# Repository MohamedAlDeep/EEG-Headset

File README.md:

# ADS1299 EEG Headset 🧠
This is a DIY / custom *electroencephalogram* reading device which is connected eeg electrodes that can connect to brain at designated areas.

It reads brain wave signals and digitizes them into the computer which is called brain-computer interface.

### Why am i doing this
I have a larger project and i want to join the competition with my pcb.

### The schematic 
This is the board schematic.

### PCB

### Mounting Part

### BOM 

| Item                  | Recommended_LCSC_PN   | Package        | JLCPCB_Type           | URL                                                                                                                                                                                                                                                                                                                                                                                                                                                                                                                                                                                                                                      | Unit Price   | Amount   | Total   |
|:----------------------|:----------------------|:---------------|:----------------------|:-----------------------------------------------------------------------------------------------------------------------------------------------------------------------------------------------------------------------------------------------------------------------------------------------------------------------------------------------------------------------------------------------------------------------------------------------------------------------------------------------------------------------------------------------------------------------------------------------------------------------------------------|:-------------|:---------|:--------|
| EEG Electrodes        |                       |                |                       | https://ar.aliexpress.com/item/1005003431845612.html?spm=a2g0o.productlist.main.8.590dhnlwhnlwyA&algo_pvid=3f3f9c85-87e4-43f8-971d-ec09da9cbb5b&algo_exp_id=3f3f9c85-87e4-43f8-971d-ec09da9cbb5b-7&pdp_ext_f=%7B%22order%22%3A%2247%22%2C%22eval%22%3A%221%22%2C%22fromPage%22%3A%22search%22%7D&pdp_npi=6%40dis%21EGP%211265.42%211265.42%21%21%2124.00%2124.00%21%40213ba8cc17621075265792275ef431%2112000025761673763%21sea%21EG%210%21ABX%211%210%21n_tag%3A-29910%3Bd%3A9358610f%3Bm03_new_user%3A-29895&curPageLogUid=TJmvYjdGyCeK&utparam-url=scene%3Asearch%7Cquery_from%3A%7Cx_object_id%3A1005003431845612%7C_p_origin_prod%3A | 26.75        | 2.0      | 53.5    |
| 100nF (Original 6.3V) | C1525                 | 402            | Basic                 | https://jlcpcb.com/partdetail/1877-CL05B104KO5NNNC/C1525                                                                                                                                                                                                                                                                                                                                                                                                                                                                                                                                                                                 | $0.01        | 4.0      | 4       |
| 10nF                  | C1524                 | 402            | Basic                 | https://jlcpcb.com/partdetail/1876-0402B103K500NT/C1524                                                                                                                                                                                                                                                                                                                                                                                                                                                                                                                                                                                  | $0.01        | 9.0      | 0.09    |
| 1μF                   | C15684                | 402            | Basic                 | https://jlcpcb.com/partdetail/MurataElectronics-GRM155R60J105KE19D/C15684                                                                                                                                                                                                                                                                                                                                                                                                                                                                                                                                                                | $0.01        | 7.0      | 0.07    |
| 10μF                  | C15849                | 402            | Basic                 |                                                                                                                                                                                                                                                                                                                                                                                                                                                                                                                                                                                                                                          | $0.01        | 1.0      | 0.01    |
| 10μF (Electrolytic)   | C86604                | CP_Elec_5x5.4  | Extended              | https://jlcpcb.com/partdetail/HonorElec-RVT1E100M0505/C86604                                                                                                                                                                                                                                                                                                                                                                                                                                                                                                                                                                             | $0.03        | 2.0      | 0.06    |
| 10kΩ                  | C25804                | 603            | Basic                 | https://jlcpcb.com/partdetail/26547-0603WAF1002T5E/C25804                                                                                                                                                                                                                                                                                                                                                                                                                                                                                                                                                                                | 0.01         | 6.0      | 0.06    |
| 1MΩ                   | C26083                | 402            | Extended              | https://jlcpcb.com/partdetail/26826-0402WGF1004TCE/C26083                                                                                                                                                                                                                                                                                                                                                                                                                                                                                                                                                                                | 0.01         | 1.0      | 0.01    |
| 5kΩ                   | C477765               | 402            | Extended              | https://jlcpcb.com/partdetail/YAGEO-RC0402FR075KL/C477765                                                                                                                                                                                                                                                                                                                                                                                                                                                                                                                                                                                | $0.01        | 16.0     | 0.16    |
| 3.3V LDO              | C5018 (AMS1117-3.3)   | SOT-223        | Basic                 | https://jlcpcb.com/partdetail/Advanced_MonolithicSystems-AMS1117_33/C6186                                                                                                                                                                                                                                                                                                                                                                                                                                                                                                                                                                | 0.16         | 1.0      | 0.16    |
| 5V LDO                | C5019 (AMS1117-5.0)   | SOT-223        | Basic                 | https://jlcpcb.com/partdetail/Advanced_MonolithicSystems-AMS1117_50/C6187                                                                                                                                                                                                                                                                                                                                                                                                                                                                                                                                                                | 0.19         | 1.0      | 0.19    |
| P-MOSFET (SOT-23)     | C10487                | SOT-23         | Basic                 | https://jlcpcb.com/partdetail/VishayIntertech-SI2301CDS_T1GE3/C10487                                                                                                                                                                                                                                                                                                                                                                                                                                                                                                                                                                     | 0.05         | 1.0      | 0.05    |
| FQD4P50 (P-MOSFET)    | C17265                | SMD:SOT-223    | Extended              | https://jlcpcb.com/partdetail/onsemi-NTF2955T1G/C17265                                                                                                                                                                                                                                                                                                                                                                                                                                                                                                                                                                                   | 0.47         | 1.0      | 0.47    |
| Conn 1×01 Pin         | C2938454              | SMT Pin Header | Basic                 | https://jlcpcb.com/partdetail/3294834-KH_2PH180_1X10P_L87/C2938454                                                                                                                                                                                                                                                                                                                                                                                                                                                                                                                                                                       | 0.05         | 2.0      | 0.1     |
| ADS1299IPAGR          | C476817               | TQFP-64(10x10) | Economic and Standard | https://jlcpcb.com/partdetail/TexasInstruments-ADS1299IPAGR/C476817                                                                                                                                                                                                                                                                                                                                                                                                                                                                                                                                                                      | 30.66        | 1.0      | 30.66   |
| Total                 |                       |                |                       |                                                                                                                                                                                                                                                                                                                                                                                                                                                                                                                                                                                                                                          |              |          | 89.59   |

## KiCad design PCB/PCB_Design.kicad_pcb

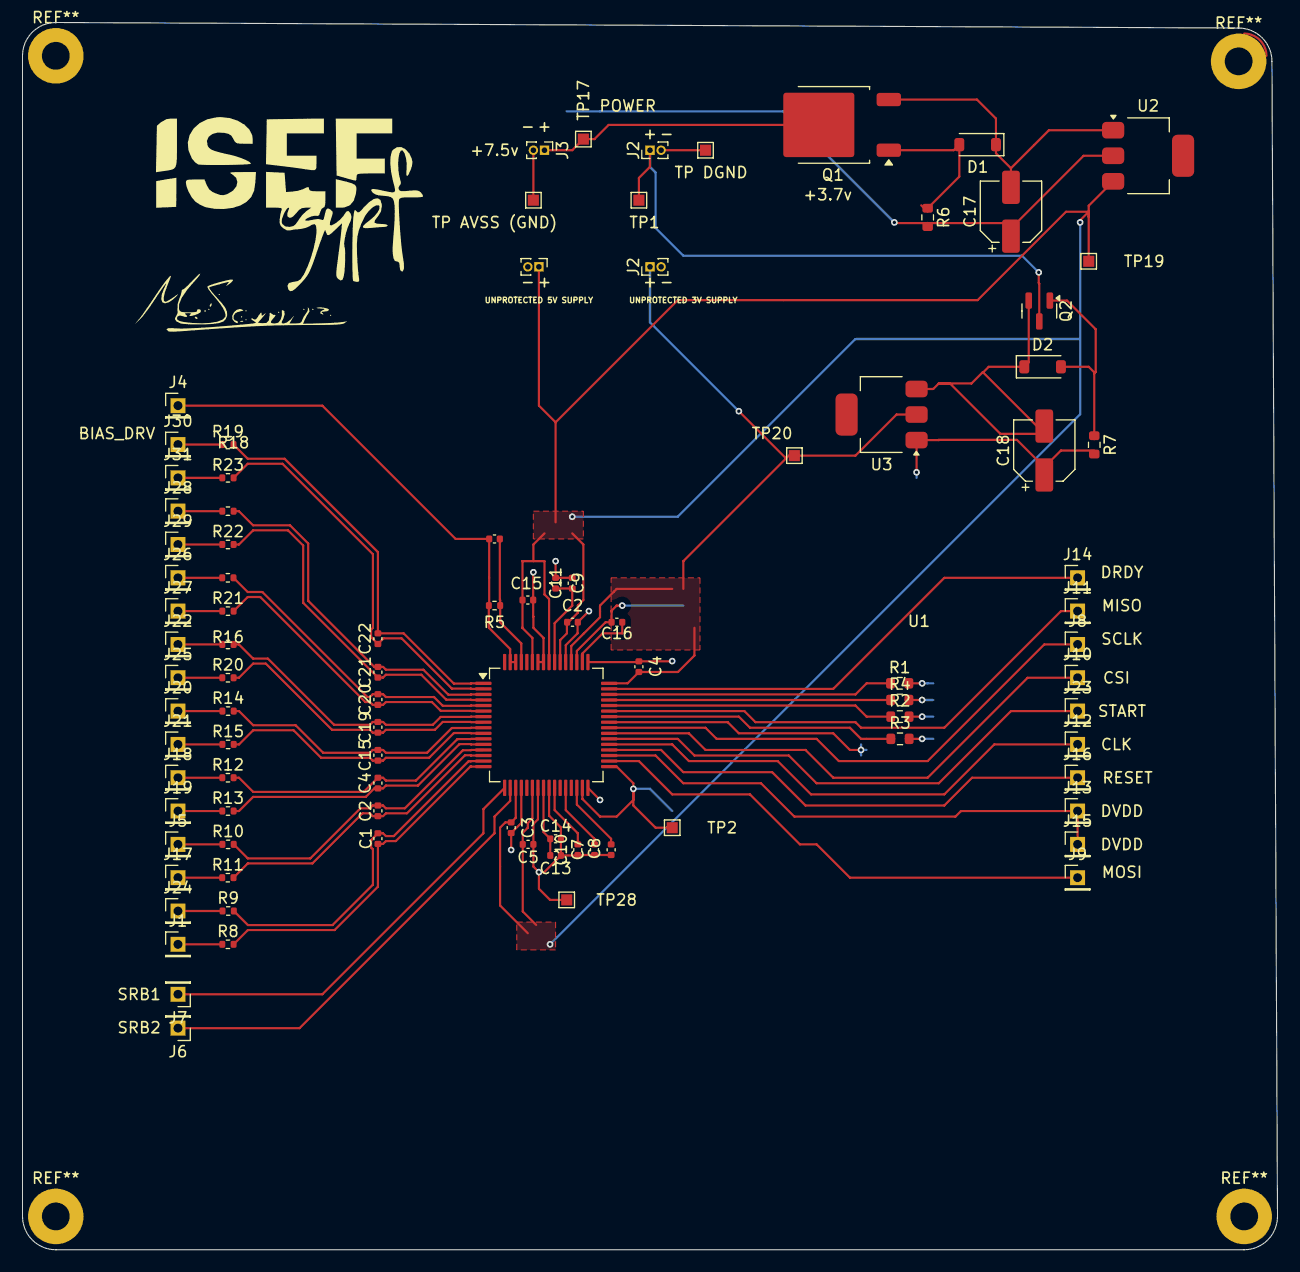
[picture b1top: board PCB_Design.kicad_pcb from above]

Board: 2 copper layers, 113.0 x 110.5 mm, 95 parts (0 on the bottom side), 52 nets.

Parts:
C1, C2, C4, C12, C15#2, C19, C20, C21, C22: 10nF; C_0402_1005Metric
C2#2, C3, C8, C9, C10, C15, C16: 1μF; C_0402_1005Metric
C4#2: 100nF; C_0402_1005Metric
C5, C11, C13: 0.1μF; C_0402_1005Metric
C7: 100μF; C_0402_1005Metric
C14: 10μF; C_0402_1005Metric
C17, C18: 10μF; CP_Elec_5x5.4
D1: BZT52C5V1-W8 5.1V Zener 500mW; D_SOD-123
D2: 1N47xxA; D_SOD-123
J1, J4, J5, J6, J7, J8, J9, J10, J11, J12, J13, J14, J15, J16, J17, J18, J19, J20, J21, J22, J23, J24, J25, J26, J27, J28, J29, J30, J31: Conn_01x01; PinHeader_1x01_P2.00mm_Vertical
J2, J2#2, J3: Conn_01x02_Pin; PinHeader_1x02_P1.00mm_Vertical
Q1: FQD4P50 (P-MOSFET); TO-252-2
Q2: IRLML6402; SOT-23
R1, R2, R3, R4, R6, R7: 10-kΩ; R_0603_1608Metric
R5: 1-MΩ; R_0402_1005Metric
R8, R9, R10, R11, R12, R13, R14, R15, R16, R17, R18, R19, R20, R21, R22, R23: 5-kΩ; R_0402_1005Metric
TP1, TP2, TP17, TP19, TP20, TP28: TestPoint; TestPoint_Pad_1.0x1.0mm
TP AVSS (GND): TestPoint; TestPoint_Pad_1.0x1.0mm
TP DGND: TestPoint; TestPoint_Pad_1.0x1.0mm
U1: ADS1299xPAG; TQFP-64_10x10mm_P0.5mm
U2: LM7805_TO220; SOT-223
U3: AMS1117-3.3; SOT-223
UNPROTECTED 5V SUPPLY: Conn_01x02_Pin; PinHeader_1x02_P1.00mm_Vertical

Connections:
+3.7V: J2#2.1, Q2.3 (D), TP1.1
+7.5V: J3.1, Q1.2 (D), TP17.1
/AVDD: C3.1, C5.2, TP19.1, U2.3 (VO)
/IN+: C1.2, C2.1, C4.1, C15#2.1, C19.1, C20.1, C21.1, C22.1, R8.2, R11.2, R13.2, R15.2, R20.2, R21.2, R22.2, R23.2, U1.2 (IN8P), U1.4 (IN7P), U1.6 (IN6P), U1.8 (IN5P), U1.10 (IN4P), U1.12 (IN3P), U1.14 (IN2P), U1.16 (IN1P)
/IN-: C1.1, C2.2, C4.2, C15#2.2, C19.2, C20.2, C21.2, C22.2, R9.2, R10.2, R12.2, R14.2, R16.2, R17.2, R18.2, R19.2, U1.1 (IN8N), U1.3 (IN7N), U1.5 (IN6N), U1.7 (IN5N), U1.9 (IN4N), U1.11 (IN3N), U1.13 (IN2N), U1.15 (IN1N)
AGND: U1.60 (BIASREF), U1.64 (RESERVED)
AVDD: C2#2.1, C15.1, UNPROTECTED 5V SUPPLY.1
AVSS: C2#2.2, C3.2, C5.1, C7.1, C8.1, C9.1, C10.1, C11.2, C13.1, C14.2, C15.2, C17.1, J3.2, R6.2, TP28.1, TP AVSS (GND).1, U1.20 (AVSS), U1.23 (AVSS), U1.25 (VREFN), U1.32 (AVSS), U1.53 (AVSS1), U1.57 (AVSS), U1.58 (AVSS), U2.2 (GND), UNPROTECTED 5V SUPPLY.2
BIAS_INV: C12.1, R5.1, U1.61 (BIASINV)
BIAS_OUT: C12.2, J4.1, R5.2, U1.62 (BIASIN), U1.63 (BIASOUT)
CLK: J12.1, U1.37 (CLK)
CSI: J10.1, U1.39 (~CS)
DGND: C4#2.1, C16.2, C18.1, J2.2, J2#2.2, R1.2, R2.2, R3.2, R4.2, R7.2, TP2.1, TP DGND.1, U1.31 (RESV1), U1.33 (DGND), U1.41 (DAISY_IN), U1.49 (DGND), U1.51 (DGND), U3.1 (GND)
DRDY: J14.1, U1.47 (~DRDY)
DVDD: C4#2.2, C16.1, J2.1, J13.1, J15.1, TP20.1, U1.35 (~PWDN), U1.48 (DVDD), U1.50 (DVDD), U1.52 (CLKSEL), U3.2 (VO)
MISO: J11.1, U1.43 (DOUT)
MOSI: J9.1, U1.34 (DIN)
unnamed: D1.2 (A), Q1.1 (G), R6.1
unnamed: C17.2, D1.1 (K), Q1.3 (S), U2.1 (VI)
unnamed: D2.2 (A), Q2.1 (G), R7.1
unnamed: C18.2, D2.1 (K), Q2.2 (S), U3.3 (VI)
unnamed: J1.1, R8.1
unnamed: J5.1, R10.1
unnamed: J17.1, R11.1
unnamed: J18.1, R12.1
unnamed: J19.1, R13.1
unnamed: J20.1, R14.1
unnamed: J21.1, R15.1
unnamed: J22.1, R16.1
unnamed: J24.1, R9.1
unnamed: J25.1, R20.1
unnamed: J26.1, R17.1
unnamed: J27.1, R21.1
unnamed: J28.1, R18.1
unnamed: J29.1, R22.1
unnamed: J30.1, R19.1
unnamed: J31.1, R23.1
unnamed: U1.19 (AVDD), U1.21 (AVDD), U1.22 (AVDD), U1.56 (AVDD), U1.59 (AVDD)
unnamed: R3.1, U1.42 (GPIO1)
unnamed: R2.1, U1.44 (GPIO2)
unnamed: R4.1, U1.45 (GPIO3)
unnamed: R1.1, U1.46 (GPIO4)
unnamed: C7.2, U1.28 (VCAP1)
unnamed: C8.2, U1.30 (VCAP2)
unnamed: C9.2, C11.1, U1.55 (VCAP3)
unnamed: C10.2, U1.26 (VCAP4)
unnamed: C13.2, C14.1, U1.24 (VREFP)
RESET: J16.1, U1.36 (~RESET)
SCLK: J8.1, U1.40 (SCLK)
SRB1: J7.1, U1.17 (SRB1)
SRB2: J6.1, U1.18 (SRB2)
START: J23.1, U1.38 (START)

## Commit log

2025-11-09 Polished
2025-11-09 After Fix
